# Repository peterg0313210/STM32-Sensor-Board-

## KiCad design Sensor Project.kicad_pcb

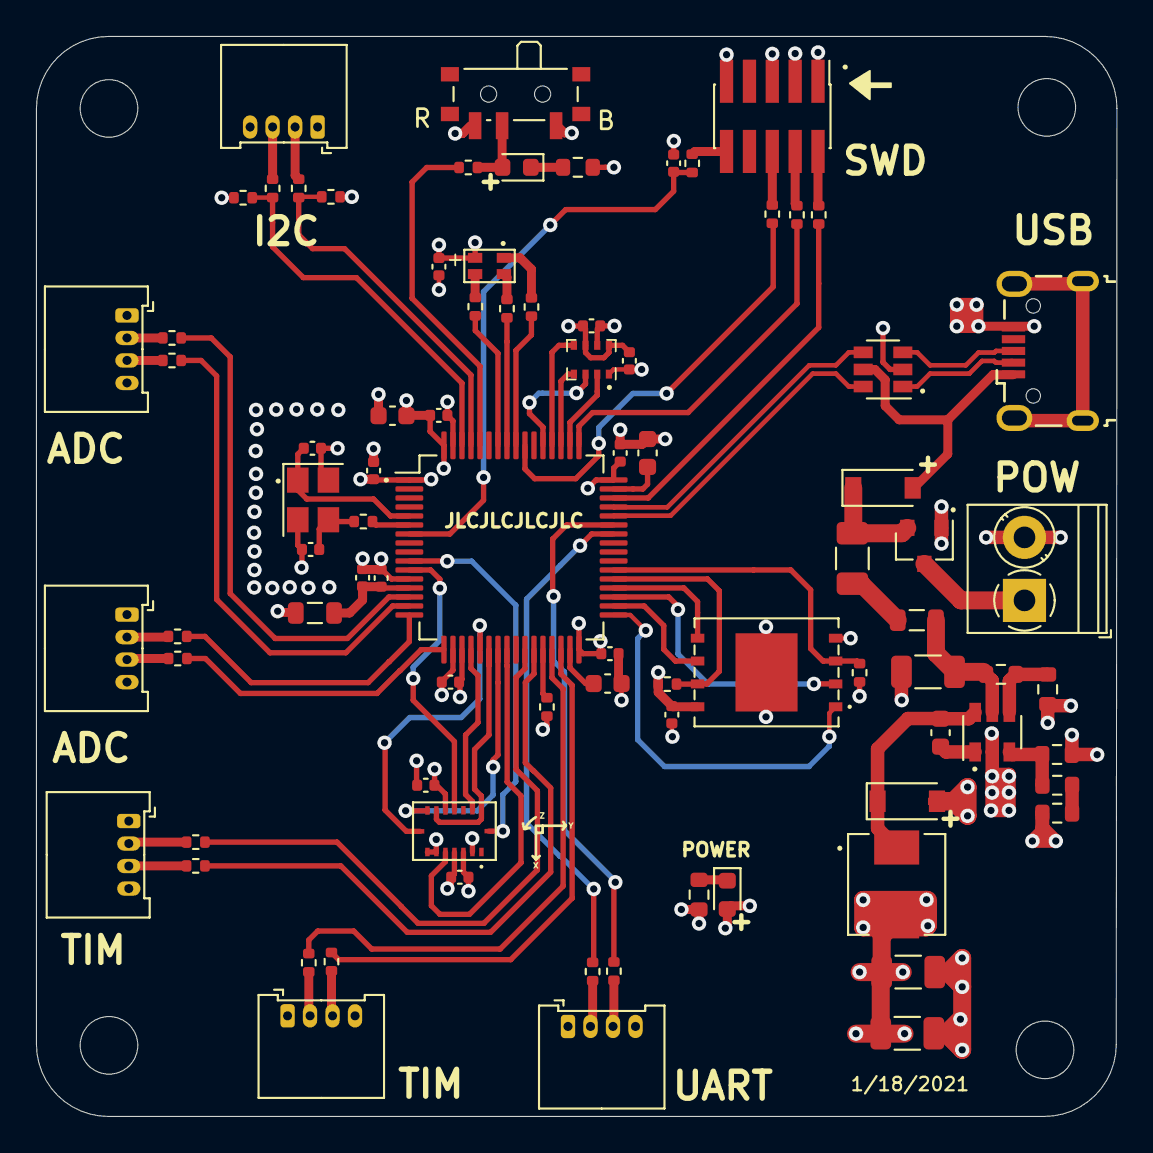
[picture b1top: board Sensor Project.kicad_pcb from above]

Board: 4 copper layers, 60.0 x 60.0 mm, 87 parts (0 on the bottom side), 82 nets.

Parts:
C1, C3, C4: 10u; C_1206_3216Metric
C2: 10n; C_0603_1608Metric
C5: 4u7; C_0603_1608Metric
C6, C8: 2u2; C_0603_1608Metric
C7, C9, C10, C11, C12, C17, C18, C19, C20, C21, C22, C23: 100n; C_0402_1005Metric
C13: 1u; C_0402_1005Metric
C14: 10n; C_0402_1005Metric
C15, C16: 12p; C_0402_1005Metric
D1, D2: B5819W; D_SOD-123
D3: GREEN; LED_0603_1608Metric
D4: RED; LED_0603_1608Metric
D5: 19-237/R6GHBHC-A01/2T; 19-237-R6GHBHC-A01-2T
F1: 250 mA; Fuse_1206_3216Metric
FB1, FB2: 600 @ 600 MHz; L_0805_2012Metric
H1, H2, H3, H4: MountingHole; MountingHole_3.2mm_M3
J1: USB_B_Micro; USB_Micro-B_Wuerth_629105150521
J2: Conn_01x02; TerminalBlock_Phoenix_PT-1,5-2-3.5-H_1x02_P3.50mm_Horizontal
J3, J4, J6, J7, J8, J9: Conn_01x04; Molex_PicoBlade_53048-0410_1x04_P1.25mm_Horizontal
J5: SWD; PinHeader_2x05_P1.27mm_Vertical_SMD
L1: 10u; L_Sunlord_MWSA0518_5.4x5.2mm
Q1: AO3401A; SOT-23
R1: 100k; R_0603_1608Metric
R2: 68k; R_0603_1608Metric
R3: 47k; R_0603_1608Metric
R4: 15k; R_0603_1608Metric
R5: 270; R_0603_1608Metric
R6: 1k5; R_0603_1608Metric
R7, R9: 2k2; R_0402_1005Metric
R8: 47; R_0402_1005Metric
R10, R15, R16, R17: 10k; R_0402_1005Metric
R11, R12, R13: 1k; R_0402_1005Metric
R14: 1k; R_0603_1608Metric
R18, R19, R20, R21, R22, R23, R24, R25, R26, R27, R28, R29, R30, R31, R32, R33: 22; R_0402_1005Metric
SW1: SW_SPDT; SW_SPDT_PCM12
U1: MP2359DJ-LF-Z; SOT-23-6
U2: STM32F405RGT6; LQFP-64_10x10mm_P0.5mm
U3: W25N01GVZEIG
U4: BMP280; Bosch_LGA-8_2x2.5mm_P0.65mm_ClockwisePinNumbering
U5: BMI088
U6: USBLC6-2SC6; SOT-23-6
Y1: 16MHz; Crystal_SMD_3225-4Pin_3.2x2.5mm

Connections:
+3.3VA: C13.1, C14.1, FB2.1, U2.13
+3V3: C3.1, C4.1, C5.1, C7.1, C9.1, C10.1, C11.1, C12.1, C17.1, C18.1, C19.1, C20.1, C21.1, C22.1, D3.2, D5.4, FB2.2, J3.1, J4.1, J5.1, J6.1, J7.1, J8.1, J9.1, L1.2, R3.1, R7.1, R9.1, R16.1, R17.1, SW1.1, U2.1, U2.19, U2.32, U2.48, U2.64, U3.8, U4.6, U4.8, U5.3, U5.11
+5V: D1.2, J1.1, U6.5
ADC1_IN0: R32.2, U2.14
ADC1_IN1: R33.2, U2.15
ADC1_IN2: R30.2, U2.16
ADC1_IN3: R31.2, U2.17
BOOT0: R10.1, U2.60
BOOT1: R15.1, U2.28
FLASH_!HOLD: R17.2, U2.37, U3.7
FLASH_!WP: R16.2, U2.38, U3.3
GND: C1.2, C3.2, C4.2, C5.2, C6.2, C7.2, C8.2, C9.2, C10.2, C11.2, C12.2, C13.2, C14.2, C15.2, C16.2, C17.2, C18.2, C19.2, C20.2, C21.2, C22.2, C23.2, D2.2, J1.5, J2.2, J3.4, J4.4, J5.3, J5.5, J5.9, J6.4, J7.4, J8.4, J9.4, Q1.1, R2.2, R5.2, R6.2, R14.2, R15.2, SW1.3, U1.2, U2.12, U2.18, U2.63, U3.4, U3.9, U4.1, U4.7, U5.2, U5.4, U5.6, U5.7, U6.2, Y1.2, Y1.4
HSE_IN: C15.1, U2.5, Y1.1
HSE_OUT: R8.1, U2.6
I2C1_SCL: R7.2, R20.2, U2.61
I2C1_SDA: R9.2, R21.2, U2.62
INT_ACC: U2.10, U5.16
INT_GYR: U2.11, U5.12
NRST: C23.1, R24.1, U2.7
unnamed: C1.1, FB1.1, R1.1, U1.5
unnamed: C2.1, D2.1, L1.1, U1.6
unnamed: C2.2, U1.1
unnamed: C6.1, U2.31
unnamed: C8.1, U2.47
unnamed: C16.1, R8.2, Y1.3
unnamed: D1.1, F1.2, Q1.2
unnamed: D3.1, R6.1
unnamed: D4.1, R14.1
unnamed: D4.2, R10.2, SW1.2
unnamed: D5.1, R11.1
unnamed: D5.2, R12.1
unnamed: D5.3, R13.1
unnamed: F1.1, FB1.2
unnamed: J3.2, R18.1
unnamed: J3.3, R19.1
unnamed: J4.2, R20.1
unnamed: J4.3, R21.1
unnamed: J5.2, R25.2
unnamed: J5.4, R28.2
unnamed: J5.6, R29.2
unnamed: J5.10, R24.2
unnamed: J6.2, R22.1
unnamed: J6.3, R23.1
unnamed: J7.2, R26.1
unnamed: J7.3, R27.1
unnamed: J8.2, R32.1
unnamed: J8.3, R33.1
unnamed: J9.2, R30.1
unnamed: J9.3, R31.1
unnamed: R1.2, R2.1, U1.4
unnamed: R3.2, R4.1, U1.3
unnamed: R4.2, R5.1
SPI1_!CS_ACC: U2.20, U5.14
SPI1_!CS_GYR: U2.24, U5.5
SPI1_MISO: U2.22, U5.10, U5.15
SPI1_MOSI: U2.23, U5.9
SPI1_SCK: U2.21, U5.8
SPI2_!CS: U2.33, U3.1
SPI2_MISO: U2.35, U3.2
SPI2_MOSI: U2.36, U3.5
SPI2_SCK: U2.34, U3.6
SPI3_!CS: U2.50, U4.2
SPI3_MISO: U2.52, U4.5
SPI3_MOSI: U2.53, U4.3
SPI3_SCK: U2.51, U4.4
SWCLK: R28.1, U2.49
SWDIO: R25.1, U2.46
SWO: R29.1, U2.55
TIM2_CH3: R26.2, U2.29
TIM2_CH4: R27.2, U2.30
TIM3_CH1: R11.2, U2.56
TIM3_CH2: R12.2, U2.57
TIM3_CH3: R22.2, U2.26
TIM3_CH4: R23.2, U2.27
TIM4_CH1: R13.2, U2.58
USART1_RX: R19.2, U2.43
USART1_TX: R18.2, U2.42
USB_CONN_D+: J1.3, U6.3
USB_CONN_D-: J1.2, U6.1
USB_D+: U2.45, U6.4
USB_D-: U2.44, U6.6
VCC: J2.1, Q1.3

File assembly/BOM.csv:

Designator,Quantity,Value,Footprint,LCSC #
"C1, C3, C4,",3,10u,Capacitor_SMD:C_1206_3216Metric,C13585
"C2,",1,10n,Capacitor_SMD:C_0603_1608Metric,C57112
"C5,",1,4u7,Capacitor_SMD:C_0603_1608Metric,C19666
"C6, C8,",2,2u2,Capacitor_SMD:C_0603_1608Metric,C23630
"C7, C9, C10, C11, C12, C17, C18, C19, C20, C21, C22, C23",12,100n,Capacitor_SMD:C_0402_1005Metric,C1525
"C13,",1,1u,Capacitor_SMD:C_0402_1005Metric,C52923
"C14,",1,10n,Capacitor_SMD:C_0402_1005Metric,C15195
"C15, C16,",2,12p,Capacitor_SMD:C_0402_1005Metric,C1547
"D1, D2,",2,B5819W,Diode_SMD:D_SOD-123,C8598
"D3,",1,GREEN,LED_SMD:LED_0603_1608Metric,C72043
"D4,",1,RED,LED_SMD:LED_0603_1608Metric,C2286
"D5,",1,19-237/R6GHBHC-A01/2T,RGB_LED:19-237-R6GHBHC-A01-2T,C60105
"F1,",1,250 mA,Fuse:Fuse_1206_3216Metric,C70068
"FB1, FB2,",2,600 @ 600 MHz,Inductor_SMD:L_0805_2012Metric,C1017
"L1,",1,10u,Inductor_SMD:L_Sunlord_MWSA0518_5.4x5.2mm,C139506
"Q1,",1,AO3401A,Package_TO_SOT_SMD:SOT-23, C15127
"R1,",1,100k,Resistor_SMD:R_0603_1608Metric,C25803
"R2,",1,68k,Resistor_SMD:R_0603_1608Metric,C23231
"R3,",1,47k,Resistor_SMD:R_0603_1608Metric,C25819
"R4,",1,15k,Resistor_SMD:R_0603_1608Metric,C22809
"R5,",1,270,Resistor_SMD:R_0603_1608Metric,C22966
"R6,",1,1k5,Resistor_SMD:R_0603_1608Metric,C22843
"R7, R9,",2,2k2,Resistor_SMD:R_0402_1005Metric,C25879
"R8,",1,47,Resistor_SMD:R_0402_1005Metric,C25118
"R10, R15, R16, R17,",4,10k,Resistor_SMD:R_0402_1005Metric,C25744
"R11, R12, R13,",3,1k,Resistor_SMD:R_0402_1005Metric,C11702
"R14,",1,1k,Resistor_SMD:R_0603_1608Metric,C21190
"R18, R19, R20, R21, R22, R23, R24, R25, R26, R27, R28, R29, R30, R31, R32, R33,",16,22,Resistor_SMD:R_0402_1005Metric,C25092
"U2,",1,STM32F405RGT6,Package_QFP:LQFP-64_10x10mm_P0.5mm,C15742
"U3,",1,W25N01GVZEIG,WinbondFlash:W25N01GVZEIG,C88868
"U4,",1,BMP280,Package_LGA:Bosch_LGA-8_2x2.5mm_P0.65mm_ClockwisePinNumbering,C233787
"U5,",1,BMI088,BMI088:BMI088,C194919
"U6,",1,USBLC6-2SC6,Package_TO_SOT_SMD:SOT-23-6, C7519
"Y1,",1,16MHz,Crystal:Crystal_SMD_3225-4Pin_3.2x2.5mm,C13738
"J1,",1,USB_B_Micro,Connector_USB:USB_Micro-B_Wuerth_629105150521,*

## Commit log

2021-01-22 adding files
